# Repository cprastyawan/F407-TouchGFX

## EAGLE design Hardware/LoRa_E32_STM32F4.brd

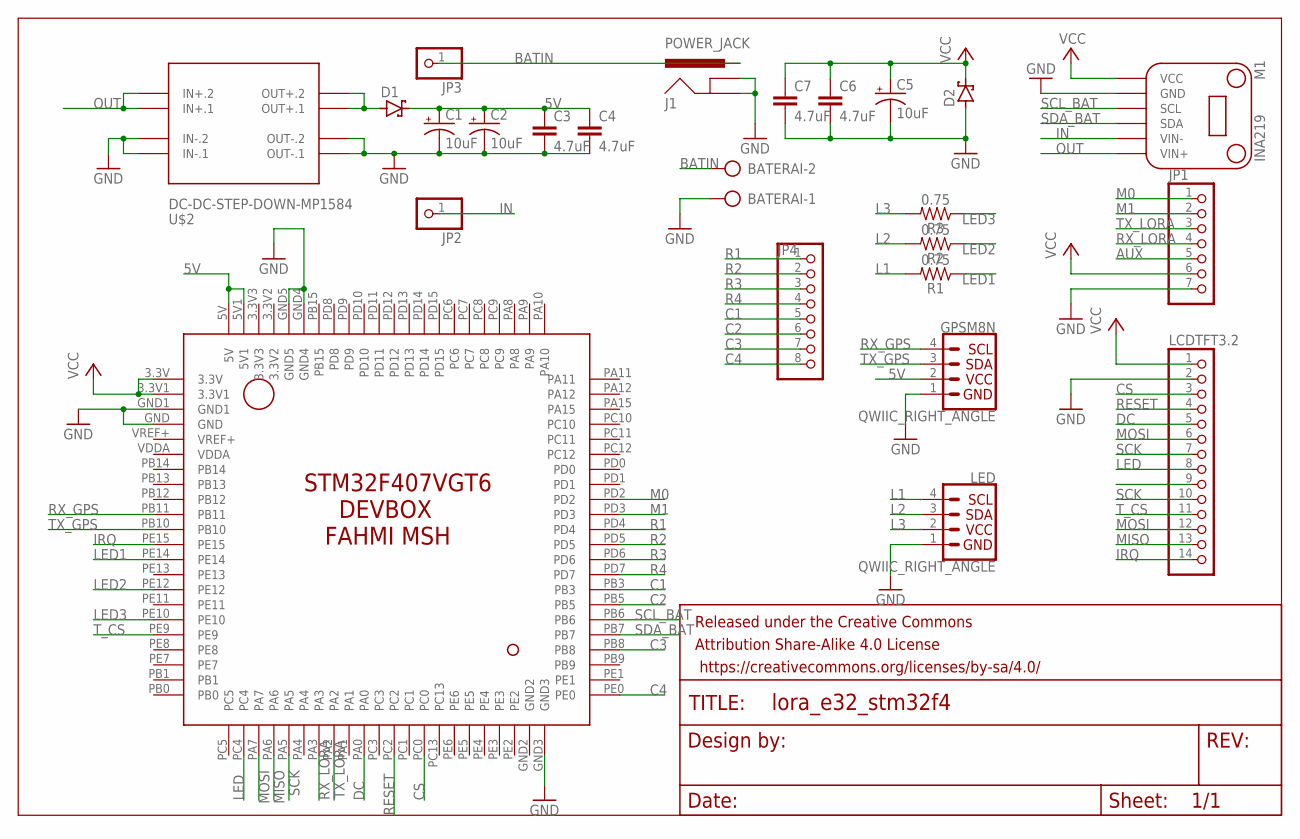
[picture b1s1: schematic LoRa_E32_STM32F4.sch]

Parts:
BATERAI: AK500/2
C1, C2, C5: 10uF; EIA3216
C3, C4, C6, C7: 4.7uF; 0805
D1, D2: SCHOTTKY-DIODESMD; SMB
FRAME1: FRAME-LEDGER; CREATIVE_COMMONS
GPSM8N: QWIIC_RIGHT_ANGLE; JST04_1MM_RA
J1: POWER_JACK; POWER_JACK_PTH
JP1: PINHD-1X7; 1X07
JP2, JP3: PINHD-1X1; 1X01
JP4: PINHD-1X8/90; 1X08/90
LCDTFT3.2: PINHD-1X14; 1X14
LED: QWIIC_RIGHT_ANGLE; JST04_1MM_RA
M1: INA219
R1, R2, R3: 0.75; 0805
U$1: STM32F4DEVBOX
U$2: DC-DC-STEP-DOWN-MP1584

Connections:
5V: C1.+, C2.+, C3.1, C4.1, D1.C, GPSM8N.2, U$1.5V, U$1.5V1
AUX: JP1.5
BATIN: BATERAI.2, J1.PWR, JP3.1
C1: JP4.5, U$1.PB3
C2: JP4.6, U$1.PB5
C3: JP4.7, U$1.PB8
C4: JP4.8, U$1.PE0
CS: LCDTFT3.2.3, U$1.PC0
DC: LCDTFT3.2.5, U$1.PA0
GND: BATERAI.1, C1.-, C2.-, C3.2, C4.2, C5.-, C6.2, C7.2, D2.A, GPSM8N.1, J1.GND, J1.GNDBREAK, JP1.7, LCDTFT3.2.2, LED.1, M1.GND, U$1.GND, U$1.GND1, U$1.GND3, U$1.GND4, U$1.GND5, U$2.IN-.1, U$2.IN-.2, U$2.OUT-.1, U$2.OUT-.2
IN: JP2.1, M1.VIN-
IRQ: LCDTFT3.2.14, U$1.PE15
L1: LED.4, R1.2
L2: LED.3, R2.2
L3: LED.2, R3.2
LED: LCDTFT3.2.8, U$1.PC4
LED1: R1.1, U$1.PE14
LED2: R2.1, U$1.PE12
LED3: R3.1, U$1.PE10
M0: JP1.1, U$1.PD2
M1: JP1.2, U$1.PD3
MISO: LCDTFT3.2.13, U$1.PA6
MOSI: LCDTFT3.2.6, LCDTFT3.2.12, U$1.PA7
unnamed: D1.A, U$2.OUT+.1, U$2.OUT+.2
OUT: M1.VIN+, U$2.IN+.1, U$2.IN+.2
R1: JP4.1, U$1.PD4
R2: JP4.2, U$1.PD5
R3: JP4.3, U$1.PD6
R4: JP4.4, U$1.PD7
RESET: LCDTFT3.2.4, U$1.PC2
RX_GPS: GPSM8N.4, U$1.PB11
RX_LORA: JP1.4, U$1.PA3
SCK: LCDTFT3.2.7, LCDTFT3.2.10, U$1.PA5
SCL_BAT: M1.SCL, U$1.PB6
SDA_BAT: M1.SDA, U$1.PB7
TX_GPS: GPSM8N.3, U$1.PB10
TX_LORA: JP1.3, U$1.PA2
T_CS: LCDTFT3.2.11, U$1.PE9
VCC: C5.+, C6.1, C7.1, D2.C, JP1.6, LCDTFT3.2.1, M1.VCC, U$1.3.3V, U$1.3.3V1

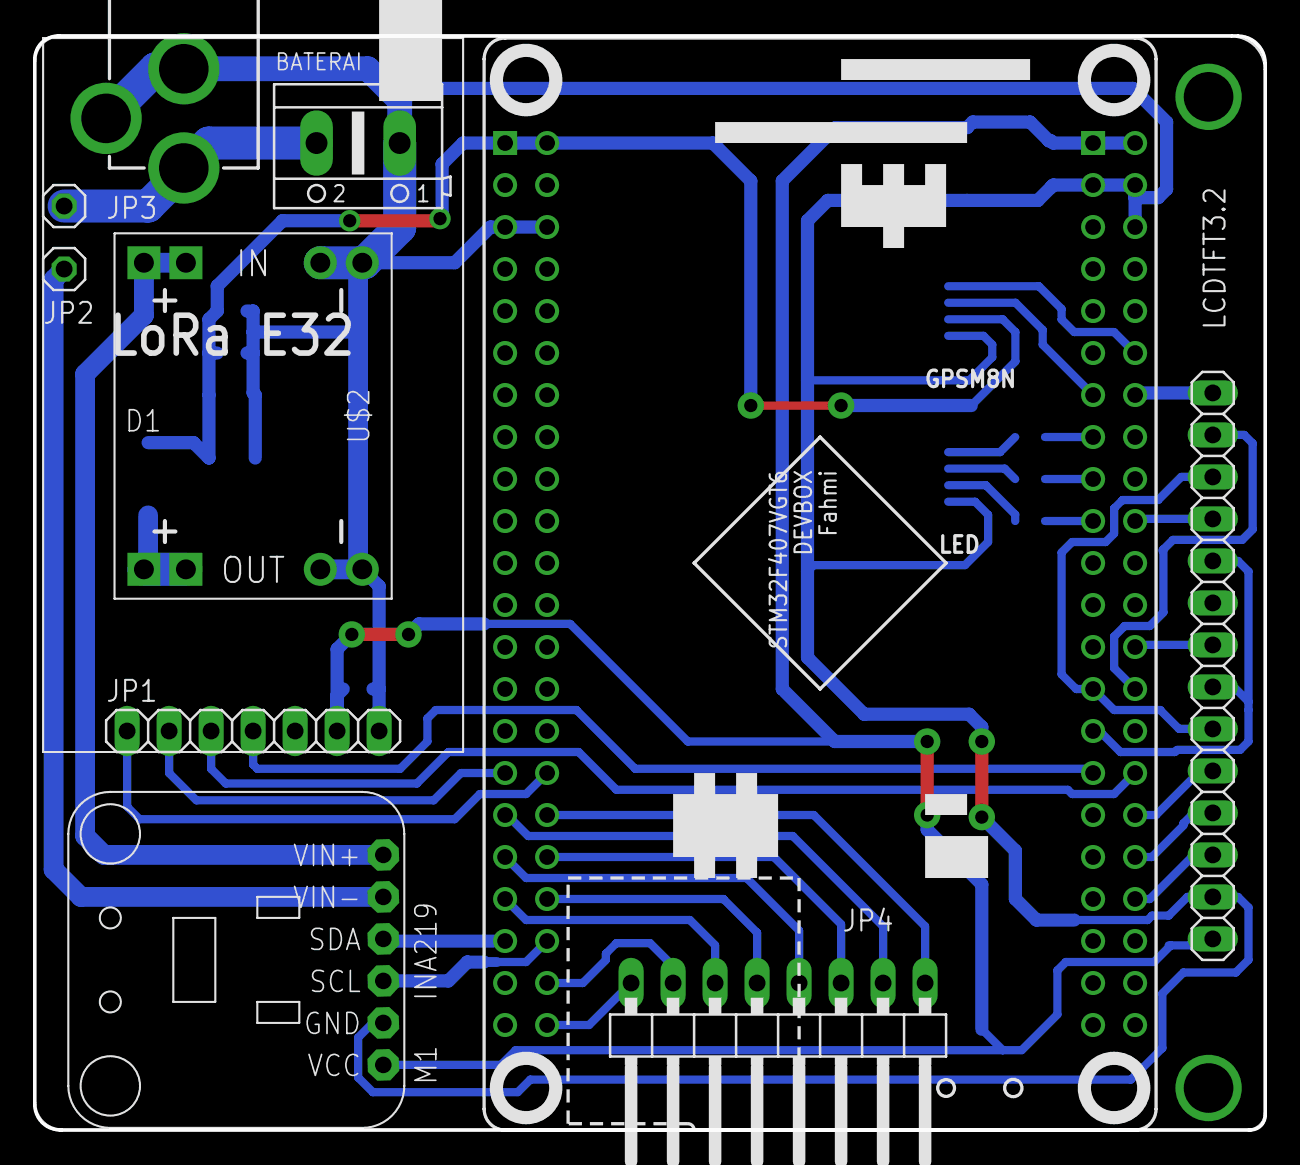
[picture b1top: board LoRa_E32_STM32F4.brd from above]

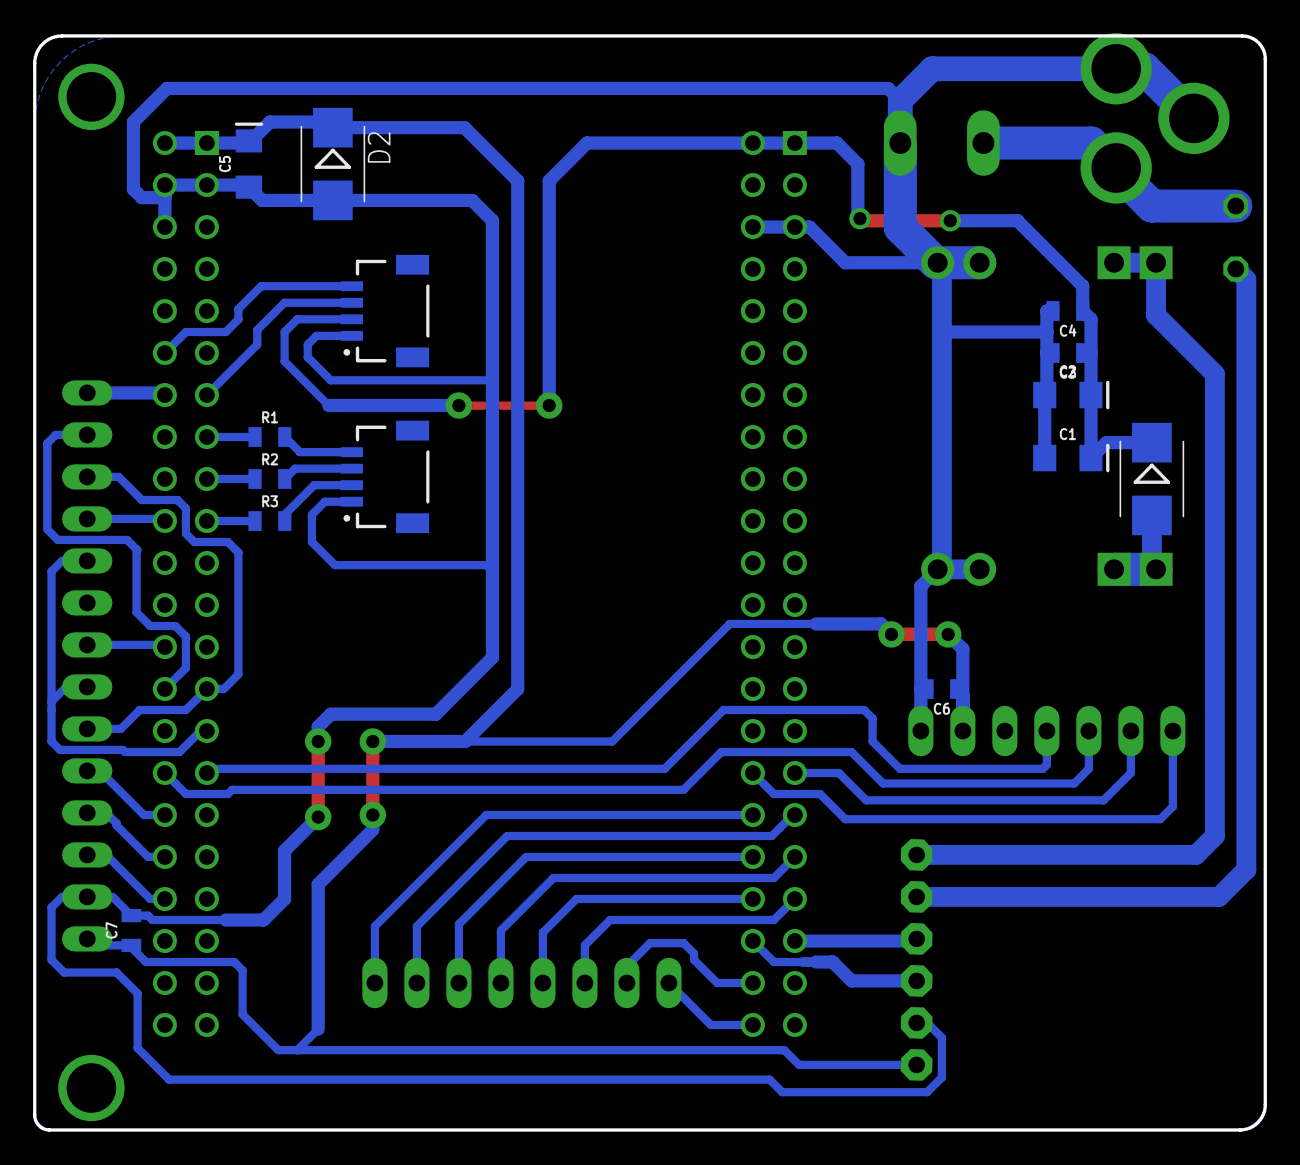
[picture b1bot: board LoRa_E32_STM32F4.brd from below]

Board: 2 copper layers, 74.4 x 66.2 mm, 25 parts (15 on the bottom side), 38 nets.

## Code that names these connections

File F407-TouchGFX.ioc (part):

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Mcu.Name=STM32F407V(E-G)Tx
Mcu.Package=LQFP100
Mcu.UserName=STM32F407VGTx
PA0-WKUP.GPIOParameters=GPIO_Label
PA0-WKUP.GPIO_Label=DC
PA0-WKUP.Signal=GPIO_Output
PA11.Signal=USB_OTG_FS_DM
PA12.Signal=USB_OTG_FS_DP
PA13.Mode=Serial_Wire
PA13.Signal=SYS_JTMS-SWDIO
PA14.Mode=Serial_Wire
PA14.Signal=SYS_JTCK-SWCLK
PA2.GPIOParameters=GPIO_PuPd,GPIO_Label
PA2.GPIO_Label=LORA_TX
PA2.GPIO_PuPd=GPIO_NOPULL
PA2.Mode=Asynchronous
PA2.Signal=USART2_TX
PA3.GPIOParameters=GPIO_PuPd,GPIO_Label
PA3.GPIO_Label=LORA_RX
PA3.GPIO_PuPd=GPIO_NOPULL
PA3.Mode=Asynchronous
PA3.Signal=USART2_RX
PA5.Mode=Full_Duplex_Master
PA5.Signal=SPI1_SCK
PA6.Mode=Full_Duplex_Master
PA6.Signal=SPI1_MISO
PA7.Mode=Full_Duplex_Master
PA7.Signal=SPI1_MOSI
PB10.GPIOParameters=GPIO_Label
PB10.GPIO_Label=GPS_TX
PB10.Mode=Asynchronous
PB10.Signal=USART3_TX
PB11.GPIOParameters=GPIO_Label
PB11.GPIO_Label=GPS_RX
PB11.Mode=Asynchronous
PB11.Signal=USART3_RX
PB3.GPIOParameters=GPIO_PuPd,GPIO_Label
PB3.GPIO_Label=KEYPAD_C1
PB3.GPIO_PuPd=GPIO_PULLUP
PB3.Signal=GPIO_Input
PB5.GPIOParameters=GPIO_PuPd,GPIO_Label
PB5.GPIO_Label=KEYPAD_C2
PB5.GPIO_PuPd=GPIO_PULLUP
PB5.Signal=GPIO_Input
PB6.Mode=I2C
PB6.Signal=I2C1_SCL
PB7.Mode=I2C
PB7.Signal=I2C1_SDA
PB8.GPIOParameters=GPIO_PuPd,GPIO_Label
PB8.GPIO_Label=KEYPAD_C3
PB8.GPIO_PuPd=GPIO_PULLUP
PB8.Signal=GPIO_Input
PB9.GPIOParameters=GPIO_PuPd,GPIO_Label
PB9.GPIO_Label=KEYPAD_C4
PB9.GPIO_PuPd=GPIO_PULLUP
PB9.Signal=GPIO_Input
PC0.GPIOParameters=GPIO_Speed,GPIO_Label
PC0.GPIO_Label=SPI1_NSS
PC0.GPIO_Speed=GPIO_SPEED_FREQ_HIGH
PC0.Signal=GPIO_Output
PC2.GPIOParameters=GPIO_Label
PC2.GPIO_Label=RESET
PC2.Signal=GPIO_Output
PC4.GPIOParameters=PinState,GPIO_Label
PC4.GPIO_Label=LED
PC4.PinState=GPIO_PIN_SET
PC4.Signal=GPIO_Output
PD2.GPIOParameters=GPIO_Label
PD2.GPIO_Label=M0
PD2.Signal=GPIO_Output
PD3.GPIOParameters=GPIO_Label
PD3.GPIO_Label=M1
PD3.Signal=GPIO_Output
PD4.GPIOParameters=PinState,GPIO_PuPd,GPIO_Label
PD4.GPIO_Label=KEYPAD_R1
PD4.GPIO_PuPd=GPIO_NOPULL
PD4.PinState=GPIO_PIN_SET
PD4.Signal=GPIO_Output
PD5.GPIOParameters=PinState,GPIO_PuPd,GPIO_Label
PD5.GPIO_Label=KEYPAD_R2
PD5.GPIO_PuPd=GPIO_NOPULL
PD5.PinState=GPIO_PIN_SET
PD5.Signal=GPIO_Output
PD6.GPIOParameters=PinState,GPIO_PuPd,GPIO_Label
PD6.GPIO_Label=KEYPAD_R3
PD6.GPIO_PuPd=GPIO_NOPULL
PD6.PinState=GPIO_PIN_SET
PD6.Signal=GPIO_Output
PD7.GPIOParameters=PinState,GPIO_PuPd,GPIO_Label
PD7.GPIO_Label=KEYPAD_R4
PD7.GPIO_PuPd=GPIO_NOPULL
PD7.PinState=GPIO_PIN_SET
PD7.Signal=GPIO_Output
PE10.GPIOParameters=GPIO_Label
PE10.GPIO_Label=LED3
PE10.Signal=GPIO_Output
PE12.GPIOParameters=GPIO_Label
PE12.GPIO_Label=LED2
PE12.Signal=GPIO_Output
PE14.GPIOParameters=GPIO_Label
PE14.GPIO_Label=LED1
PE14.Signal=GPIO_Output
PE15.GPIOParameters=GPIO_Label
PE15.GPIO_Label=IRQ
PE15.Signal=GPIO_Input
PE9.GPIOParameters=GPIO_Speed,PinState,GPIO_Label
PE9.GPIO_Label=T_CS
PE9.GPIO_Speed=GPIO_SPEED_FREQ_VERY_HIGH
PE9.PinState=GPIO_PIN_SET
PE9.Signal=GPIO_Output
PH0-OSC_IN.Mode=HSE-External-Oscillator
PH0-OSC_IN.Signal=RCC_OSC_IN
PH1-OSC_OUT.Mode=HSE-External-Oscillator
PH1-OSC_OUT.Signal=RCC_OSC_OUT
RCC.HSE_VALUE=8000000
RCC.SYSCLKFreq_VALUE=168000000
RCC.SYSCLKSource=RCC_SYSCLKSOURCE_PLLCLK
board=custom

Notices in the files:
parts and their libraries:
diy-modules: Released under the Creative Commons Attribution 4.0 International License: http://creativecommons.org/licenses/by/4.0
SparkFun-Connectors: Licensing: Creative Commons ShareAlike 4.0 International - https://creativecommons.org/licenses/by-sa/4.0
